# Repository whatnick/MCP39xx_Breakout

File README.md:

# MCP39xx Breakout
Breakouts for MCP39xx series single-phase energy monitors.

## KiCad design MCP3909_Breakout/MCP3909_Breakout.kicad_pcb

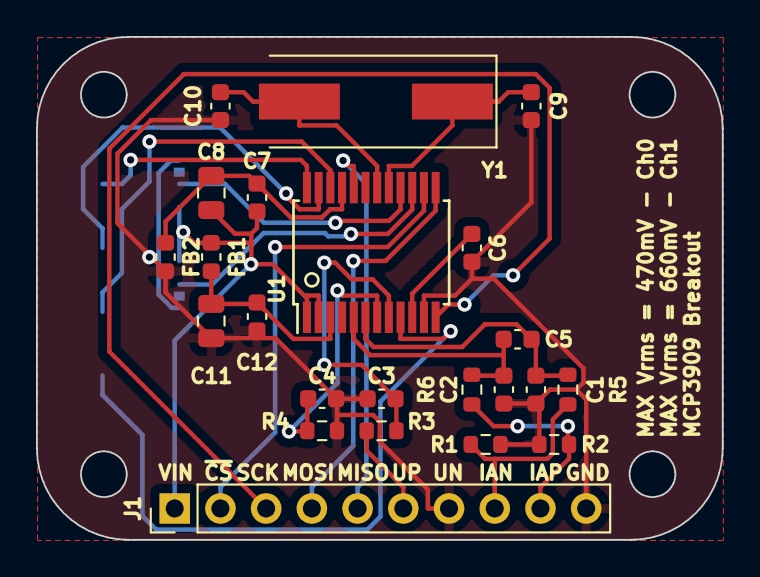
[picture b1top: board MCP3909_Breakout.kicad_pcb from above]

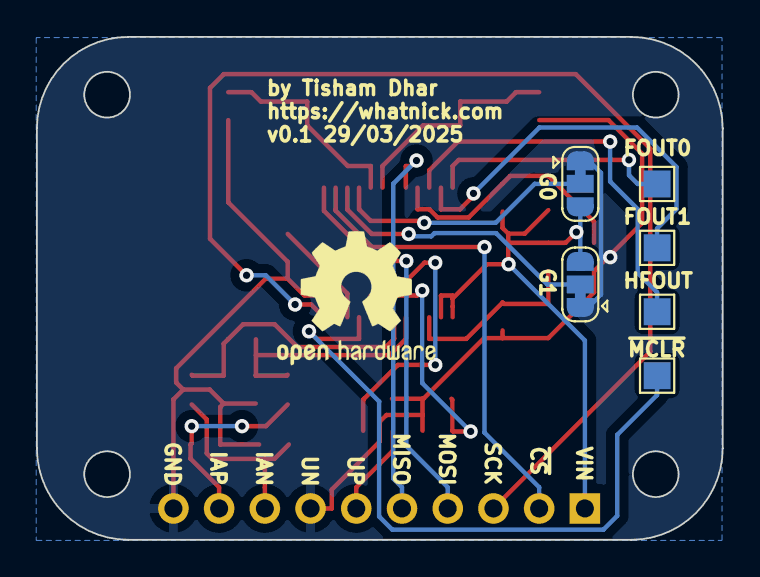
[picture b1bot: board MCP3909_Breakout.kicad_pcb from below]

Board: 2 copper layers, 38.1 x 27.9 mm, 30 parts (7 on the bottom side), 24 nets.

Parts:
C1, C2, C3, C4: 33n; C_0603_1608Metric
C5: 100p; C_0603_1608Metric
C6, C7, C12: 100n; C_0603_1608Metric
C8, C11: 4.7u; C_0805_2012Metric
C9, C10: 15p; C_0603_1608Metric
FB1, FB2: FerriteBead_Small; L_0603_1608Metric
J1: Conn_01x10; PinHeader_1x10_P2.54mm_Vertical
JP1, JP2: SolderJumper_3_Bridged12; SolderJumper-3_P1.3mm_Bridged12_RoundedPad1.0x1.5mm
R1, R2: 2R2; R_0603_1608Metric
R3, R4, R5, R6: 1k; R_0603_1608Metric
SYM1: Logo_Open_Hardware_Small; OSHW-Logo2_9.8x8mm_SilkScreen
TP1, TP2, TP3, TP4: TestPoint; TestPoint_Pad_1.5x1.5mm
U1: MCP3909; SSOP-24_5.3x8.2mm_P0.65mm
Y1: Crystal_Small; Crystal_SMD_HC49-SD

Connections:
FOUT0: TP1.1, U1.24 (FOUT0)
FOUT1: TP2.1, U1.23 (FOUT1)
G0: JP1.2 (C), U1.16 (G0)
G1: JP2.2 (C), U1.15 (G1)
GND: C1.2, C2.1, C3.2, C4.1, C6.2, C9.2, C10.2, C11.2, C12.2, FB2.2, J1.7, J1.10, JP1.1 (A), JP2.1 (A), R1.2, R2.1, R4.1, U1.11 (AGND)
GNDD: C7.1, C8.1, FB2.1, U1.21 (DGND)
HFOUT: TP3.1, U1.22 (HFOUT)
IAN: C1.1, C5.1, R5.2, U1.6 (CH0-)
IAN_IN: J1.8, R1.1, R5.1
IAP: C2.2, C5.2, R6.2, U1.5 (CH0+)
IAP_IN: J1.9, R2.2, R6.1
MISO/NEG: J1.5, U1.20 (SDO/NEG)
MOSI/F1: J1.4, U1.13 (SDI/F1)
unnamed: C11.1, C12.1, FB1.2, U1.3 (AVDD)
unnamed: C9.1, U1.17 (OSC1), Y1.1
unnamed: C10.1, U1.18 (OSC2), Y1.2
unnamed: C6.1, U1.10 (REFIN/OUT)
SCK/F2: J1.3, U1.12 (SCK/F2)
UN: C4.2, R4.2, U1.7 (CH1-)
UP: C3.1, R3.2, U1.8 (CH1+)
UP_IN: J1.6, R3.1
VIN: C7.2, C8.2, FB1.1, J1.1, JP1.3 (B), JP2.3 (B), U1.1 (DVDD), U1.2 (HPF)
~CS/F0: J1.2, U1.14 (~CS/F0)
~MCLR: TP4.1, U1.9 (~MCLR)

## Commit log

2025-03-09 Initial footprint
2025-03-09 Fix naming
2025-03-22 Complete wiring up most things
2025-03-23 First go at place-n-route
2025-03-29 Complete routing
2025-04-13 Produce fabrication outputs
